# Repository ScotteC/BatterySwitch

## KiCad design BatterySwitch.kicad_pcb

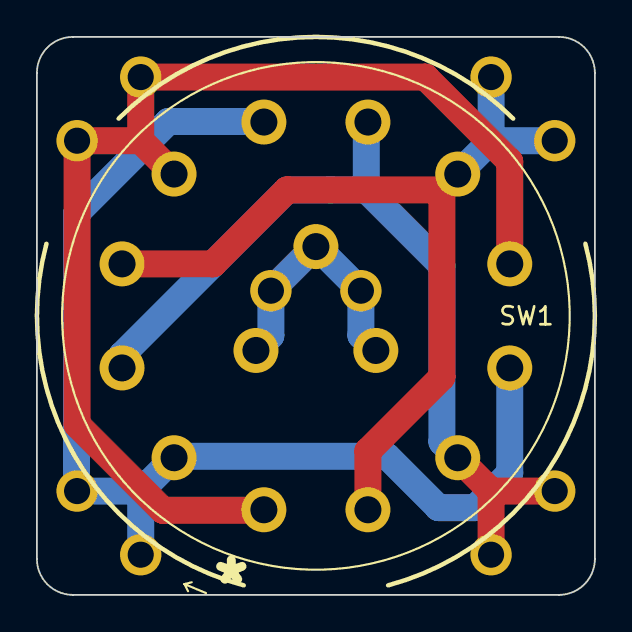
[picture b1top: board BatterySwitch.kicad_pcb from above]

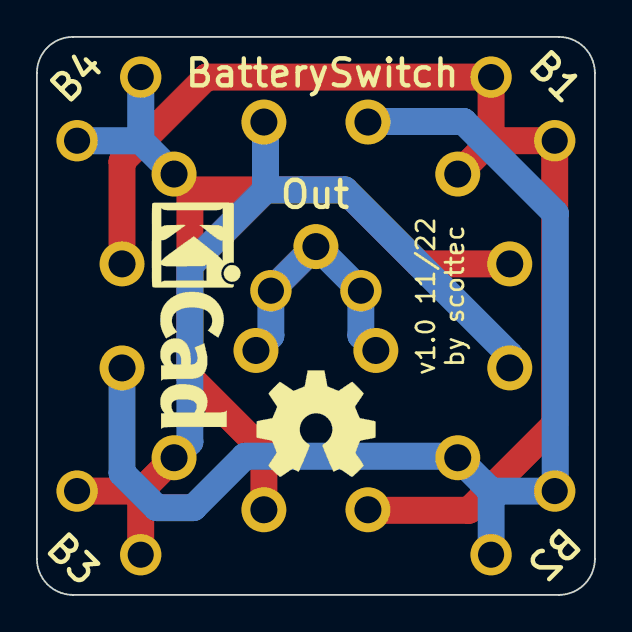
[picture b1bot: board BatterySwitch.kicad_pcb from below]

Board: 2 copper layers, 31.0 x 31.0 mm, 6 parts (5 on the bottom side), 5 nets.

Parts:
J1: B1; Tab_6.35_P5.00_Vertical
J2: B2; Tab_6.35_P5.00_Vertical
J3: B3; Tab_6.35_P5.00_Vertical
J4: B4; Tab_6.35_P5.00_Vertical
J5: Out; Tab_6.35_P5.00_Vertical
SW1: SW_Rotary3x4; Lorlin_CKxxx_3x4pos

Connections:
/Vcc: J5.1, SW1.13, SW1.14, SW1.15
Bat1: J1.1, SW1.1, SW1.5, SW1.9
Bat2: J2.1, SW1.2, SW1.6, SW1.10
Bat3: J3.1, SW1.3, SW1.7, SW1.11
Bat4: J4.1, SW1.4, SW1.8, SW1.12
